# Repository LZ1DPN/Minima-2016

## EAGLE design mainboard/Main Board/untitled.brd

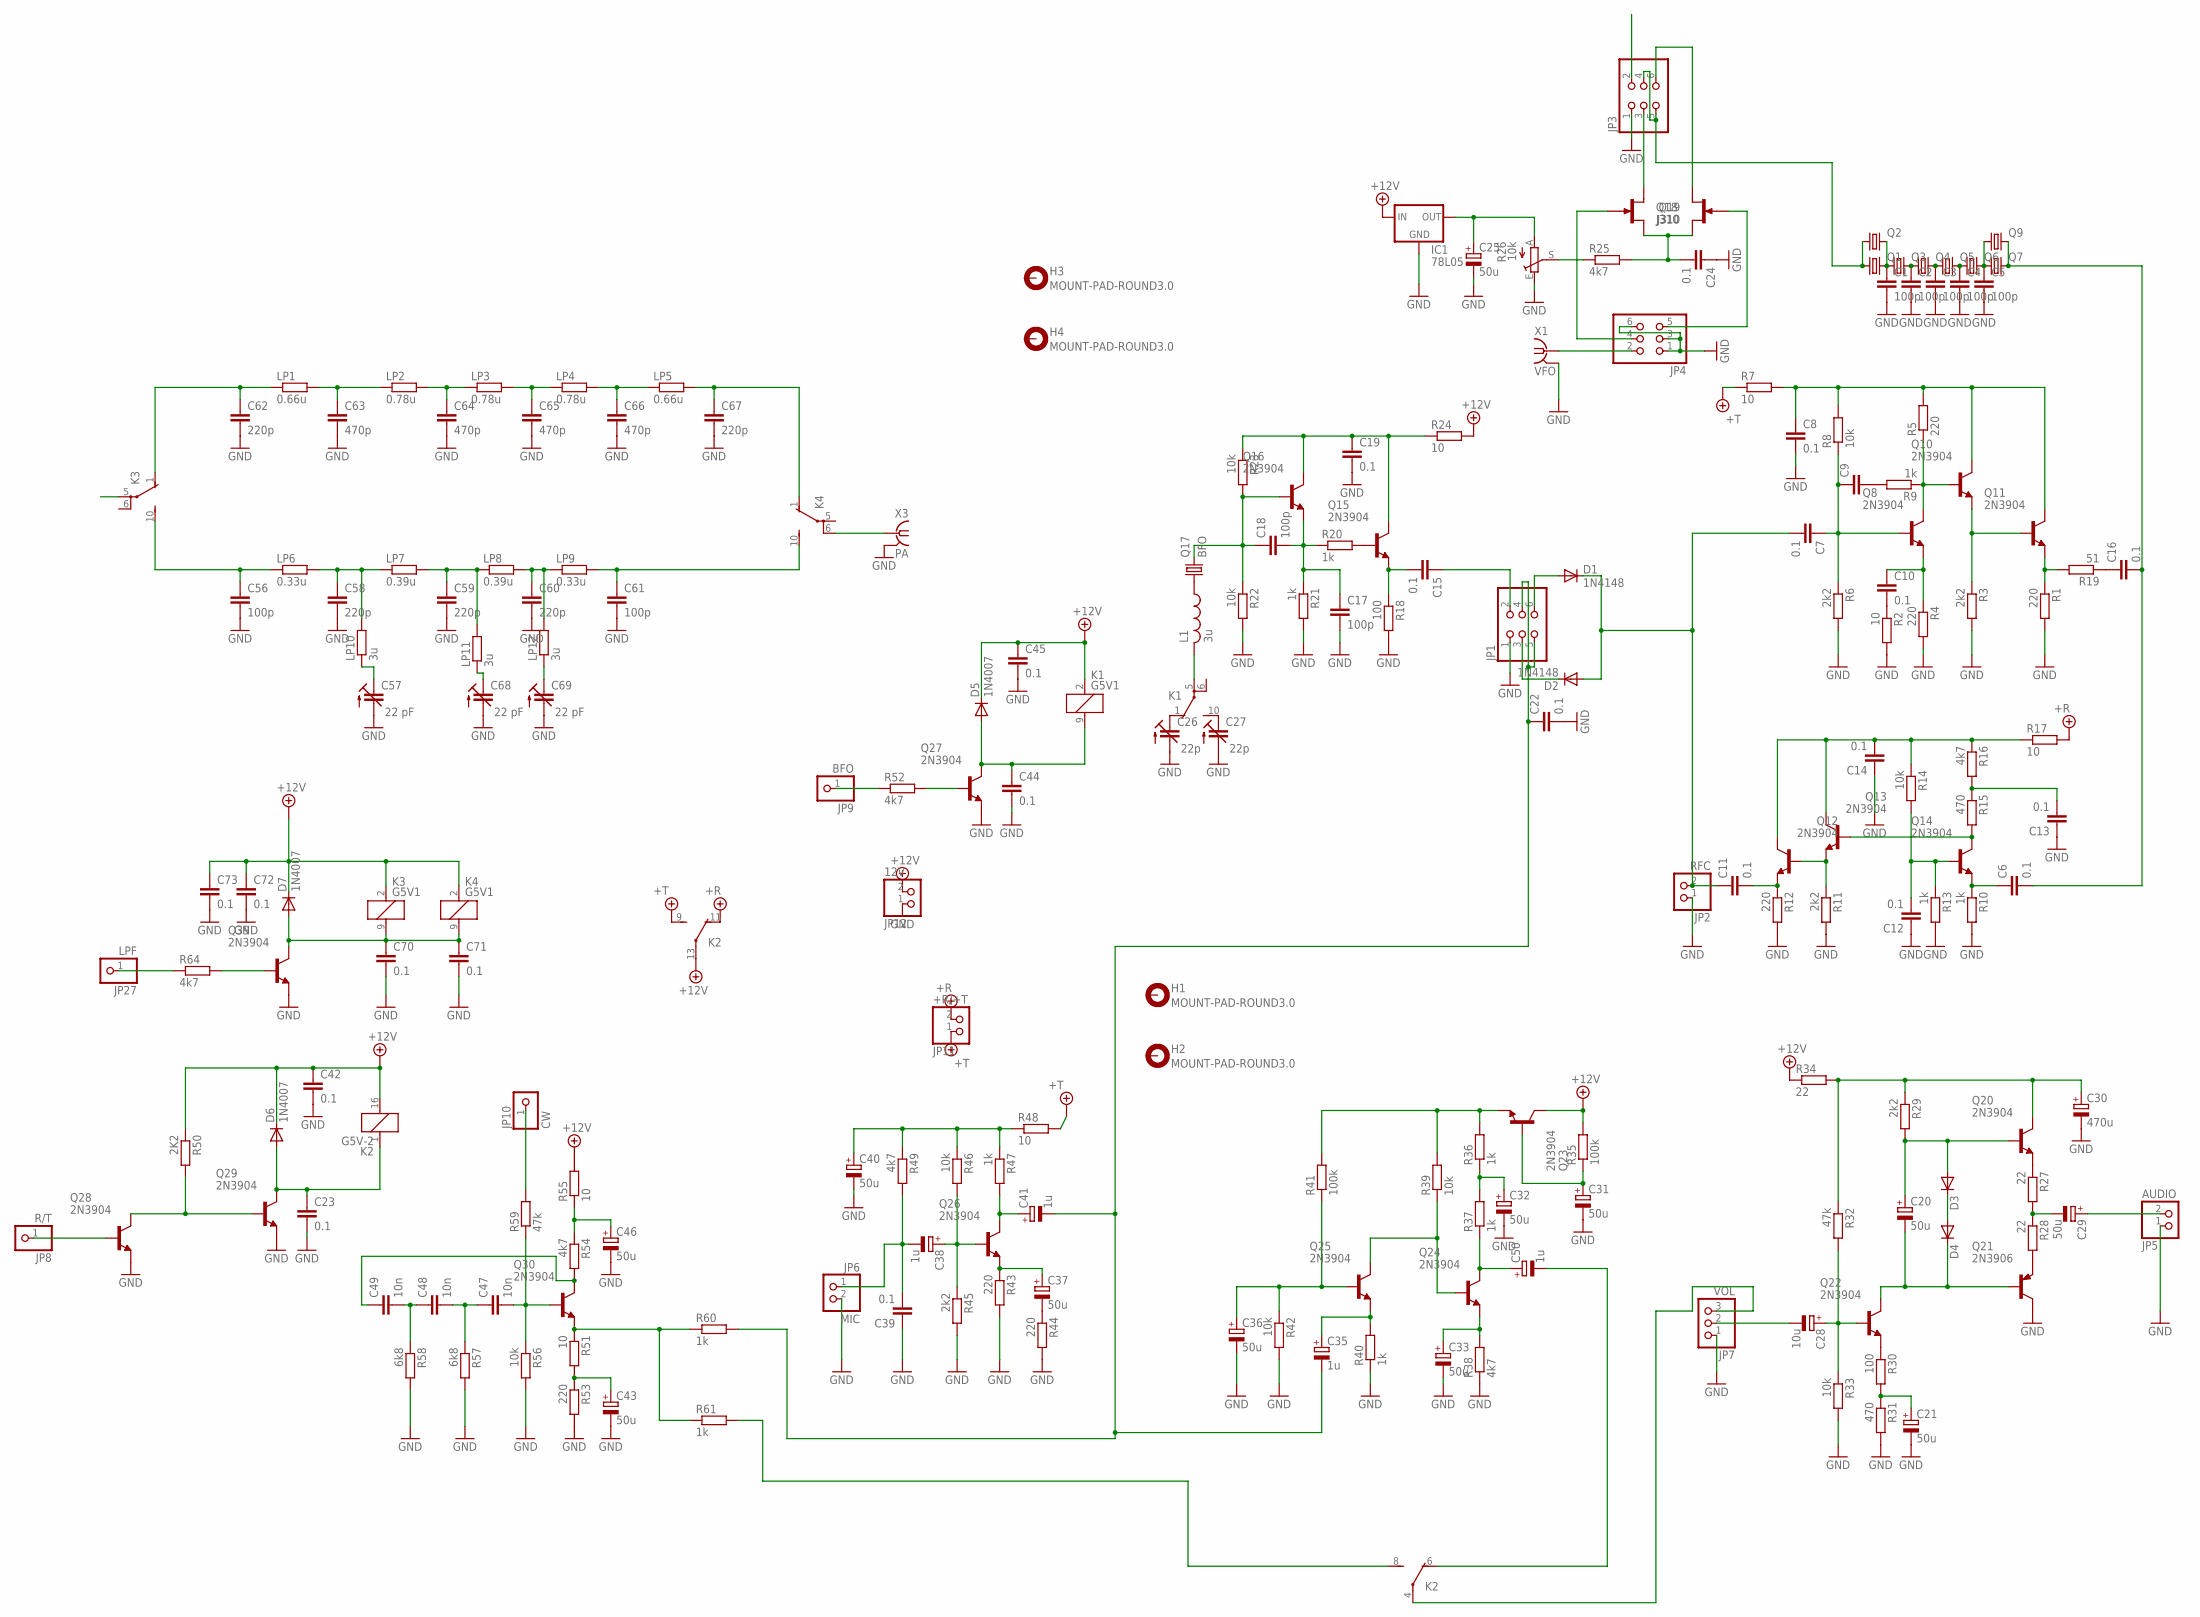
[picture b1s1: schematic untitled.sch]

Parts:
C1, C2, C3, C4, C5: 100p; C1206
C6, C7, C8, C10, C11, C12, C13, C14, C15, C16, C19, C22, C23, C24, C39, C42, C44, C45, C70, C71, C72, C73: 0.1; C050-024X044
C9: C-EU050-024X044; C050-024X044
C17, C18, C56, C61: 100p; C050-024X044
C20, C21, C25, C29, C31, C32, C33, C36, C37, C40, C43, C46: 50u; E2,5-5
C26, C27: 22p; CTRIMTZ03
C28: 10u; E2,5-5
C30: 470u; E2,5-5
C35, C38, C41: 1u; E2,5-5
C47, C48, C49: 10n; C050-024X044
C50: 1u; E5-4
C57, C68, C69: 22 pF; CTRIMTZ03
C58, C59, C60, C62, C67: 220p; C050-024X044
C63, C64, C65, C66: 470p; C050-024X044
D1, D2: 1N4148; D-5
D3, D4: DIODE-D-5; D-5
D5, D6, D7: 1N4007; D-5
H1, H2, H3, H4: MOUNT-PAD-ROUND3.0; 3,0-PAD
IC1: 78L05; 78LXX
JP1, JP3, JP4: PINHD-2X3; 2X03
JP2: RFC; 1X02
JP5: AUDIO; 1X02
JP6: MIC; 1X02
JP7: VOL; 1X03
JP8: R/T; 1X01
JP9: BFO; 1X01
JP10: CW; 1X01
JP11: +R/+T; 1X02
JP12: 12V; 1X02
JP27: LPF; 1X01
K1, K3, K4: G5V1
K2: G5V-2
L1: 3u; 0207/2V
LP1, LP5: 0.66u; 0204/5
LP2, LP3, LP4: 0.78u; 0204/5
LP6, LP9: 0.33u; 0204/5
LP7, LP8: 0.39u; 0204/5
LP10, LP11, LP12: 3u; 0204/5
Q1, Q2, Q3, Q4, Q5, Q6, Q7, Q9: CRYSTALHC49S; HC49/S
Q8, Q10, Q11, Q12, Q13, Q14, Q15, Q16, Q20, Q22, Q23, Q24, Q25, Q26, Q27, Q28, Q29, Q30, Q39: 2N3904; TO92
Q17: BFO; HC49/S
Q18, Q19: J310; TO92R
Q21: 2N3906; TO92
R1, R4, R5, R12, R43, R44, R53: 220; 0204/5
R2, R7, R17, R24, R48, R51, R55: 10; 0204/5
R3, R6, R11, R29, R45: 2k2; 0204/5
R8, R14, R22, R23, R33, R39, R42, R46, R56: 10k; 0204/5
R9, R10, R13, R20, R21, R36, R37, R40, R47, R60, R61: 1k; 0204/5
R15, R31: 470; 0204/5
R16, R25, R38, R49, R52, R54, R64: 4k7; 0204/5
R18, R30: 100; 0204/5
R19: 51; 0204/5
R26: 10k; CA6V
R27, R28, R34: 22; 0204/5
R32, R59: 47k; 0204/5
R35, R41: 100k; 0204/5
R50: 2K2; 0204/5
R57, R58: 6k8; 0204/5
X1: VFO; BU-SMA-V
X3: PA; BU-SMA-V

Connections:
+5V/1: JP11.2, K2.11 (O), R17.2
+5V/2: JP11.1, K2.9 (S), R7.1, R48.2
+12V: C42.1, C45.1, C72.1, C73.1, D5.C, D6.C, D7.C, IC1.IN, JP12.2, K1.2 (1), K2.13, K2.16 (2), K3.2 (1), K4.2 (1), Q23.1 (C), R24.2, R34.1, R35.2, R50.1, R55.2
GND: C1.2, C2.2, C3.2, C4.2, C5.2, C8.2, C12.1, C13.1, C14.1, C17.2, C19.2, C21.-, C22.2, C23.2, C24.1, C25.-, C26.2 (A), C27.2 (A), C30.-, C31.-, C32.-, C33.-, C36.-, C39.1, C40.-, C42.2, C43.-, C44.2, C45.2, C46.-, C56.2, C57.2 (A), C58.2, C59.2, C60.2, C61.2, C62.2, C63.2, C64.2, C65.2, C66.2, C67.2, C68.2 (A), C69.2 (A), C70.2, C71.2, C72.2, C73.2, IC1.GND, JP1.1, JP2.1, JP3.1, JP4.1, JP4.3, JP4.6, JP5.1, JP6.2, JP7.1, JP12.1, Q21.1 (C), Q27.3 (E), Q28.3 (E), Q29.3 (E), Q39.3 (E), R1.2, R2.2, R3.2, R4.2, R6.2, R10.2, R11.2, R12.2, R13.2, R18.2, R21.2, R22.2, R26.E, R31.2, R33.2, R38.1, R40.1, R42.2, R43.2, R44.2, R45.2, R53.2, R56.2, R57.2, R58.2, X1.2 (GND), X1.3 (GND), X1.4 (GND), X1.5 (GND), X3.2 (GND), X3.3 (GND), X3.4 (GND), X3.5 (GND)
unnamed: C1.1, Q1.2, Q2.2, Q3.1
unnamed: C2.1, Q3.2, Q4.1
unnamed: C3.1, Q4.2, Q5.1
unnamed: C4.1, Q5.2, Q6.1
unnamed: C5.1, Q6.2, Q7.1, Q9.1
unnamed: C6.2, C16.2, Q7.2, Q9.2
unnamed: C26.1 (E), K1.1 (O)
unnamed: C10.1, Q8.3 (E), R4.1
unnamed: C10.2, R2.1
unnamed: C7.1, C9.1, Q8.2 (B), R6.1, R8.1
unnamed: Q8.1 (C), Q10.2 (B), R5.1, R9.1
unnamed: Q10.3 (E), Q11.2 (B), R3.1
unnamed: Q11.3 (E), R1.1, R19.2
unnamed: C8.1, Q10.1 (C), Q11.1 (C), R5.2, R7.2, R8.2
unnamed: C16.1, R19.1
unnamed: C9.2, R9.2
unnamed: Q12.2 (B), Q13.3 (E), R11.1
unnamed: C11.2, Q12.3 (E), R12.1
unnamed: C14.2, Q12.1 (C), Q13.1 (C), R14.1, R16.1, R17.1
unnamed: C27.1 (E), K1.10 (S)
unnamed: C12.2, Q14.2 (B), R13.1, R14.2
unnamed: C6.1, Q14.3 (E), R10.1
unnamed: Q13.2 (B), Q14.1 (C), R15.2
unnamed: C13.2, R15.1, R16.2
unnamed: C15.2, Q15.3 (E), R18.1
unnamed: Q15.2 (B), R20.2
unnamed: C17.1, C18.2, Q16.3 (E), R20.1, R21.1
unnamed: C19.1, Q15.1 (C), Q16.1 (C), R23.1, R24.1
unnamed: C15.1, JP1.2
unnamed: C18.1, Q16.2 (B), Q17.2, R22.1, R23.2
unnamed: L1.1, Q17.1
unnamed: K1.5, L1.2
unnamed: R25.1, R26.S
unnamed: Q20.3 (E), R27.1
unnamed: Q27.2 (B), R52.2
unnamed: D1.A, JP1.6
unnamed: D2.C, JP1.3
unnamed: C7.2, C11.1, D1.C, D2.A, JP2.2
unnamed: JP3.4, JP3.5, Q1.1, Q2.1
unnamed: JP3.3, Q18.D
unnamed: JP3.6, Q19.D
unnamed: C24.2, Q18.S, Q19.S, R25.2
unnamed: JP4.5, Q19.G
unnamed: JP4.4, Q18.G
unnamed: C29.-, R27.2, R28.1
unnamed: JP4.2, X1.1
unnamed: Q21.3 (E), R28.2
unnamed: C25.+, IC1.OUT, R26.A
unnamed: D3.C, D4.A
unnamed: C20.-, D4.C, Q21.2 (B), Q22.1 (C)
unnamed: C20.+, D3.A, Q20.2 (B), R29.2
unnamed: C30.+, Q20.1 (C), R29.1, R32.1, R34.2
unnamed: Q22.3 (E), R30.1
unnamed: C21.+, R30.2, R31.1
unnamed: C28.+, Q22.2 (B), R32.2, R33.1
unnamed: C29.+, JP5.2
unnamed: C28.-, JP7.2
unnamed: C31.+, Q23.2 (B), R35.1
unnamed: Q23.3 (E), R36.2, R39.2, R41.2
unnamed: C32.+, R36.1, R37.2
unnamed: C50.+, Q24.1 (C), R37.1
unnamed: C33.+, Q24.3 (E), R38.2
unnamed: Q24.2 (B), Q25.1 (C), R39.1
unnamed: JP9.1, R52.1
unnamed: C35.+, Q25.3 (E), R40.2
unnamed: C36.+, Q25.2 (B), R41.1, R42.1
unnamed: C37.+, Q26.3 (E), R43.1
unnamed: C37.-, R44.1
unnamed: C38.+, Q26.2 (B), R45.1, R46.2
unnamed: C41.+, Q26.1 (C), R47.2
unnamed: C40.+, R46.1, R47.1, R48.1, R49.1
unnamed: C38.-, C39.2, JP6.1, R49.2
unnamed: JP7.3, K2.4
unnamed: C22.1, C35.-, C41.-, JP1.4, JP1.5, R60.2
unnamed: C50.-, K2.6 (O)
unnamed: JP8.1, Q28.2 (B)
unnamed: C23.1, D6.A, K2.1, Q29.1 (C)
unnamed: Q28.1 (C), Q29.2 (B), R50.2
unnamed: C44.1, D5.A, K1.9 (2), Q27.1 (C)
unnamed: C57.1 (E), LP10.1
unnamed: Q30.3 (E), R51.1, R60.1, R61.1
unnamed: C43.+, R51.2, R53.1
unnamed: C49.1, Q30.1 (C), R54.2
unnamed: C46.+, R54.1, R55.1
unnamed: C47.2, Q30.2 (B), R56.1, R59.1
unnamed: C47.1, C48.2, R57.1
unnamed: C48.1, C49.2, R58.1
unnamed: C68.1 (E), LP11.1
unnamed: JP10.1, R59.2
unnamed: K2.8 (S), R61.2
unnamed: C56.1, K3.10 (S), LP6.1
unnamed: C58.1, LP6.2, LP7.1, LP10.2
unnamed: C59.1, LP7.2, LP8.1, LP11.2
unnamed: C60.1, LP8.2, LP9.1, LP12.2
unnamed: C61.1, K4.10 (S), LP9.2
unnamed: C62.1, K3.1 (O), LP1.1
unnamed: C63.1, LP1.2, LP2.1
unnamed: C64.1, LP2.2, LP3.1
unnamed: C65.1, LP3.2, LP4.1
unnamed: C66.1, LP4.2, LP5.1
unnamed: C67.1, K4.1 (O), LP5.2
unnamed: K4.6, X3.1
unnamed: JP3.2, K3.5
unnamed: C69.1 (E), LP12.1
unnamed: Q39.2 (B), R64.2
unnamed: JP27.1, R64.1
unnamed: C70.1, C71.1, D7.A, K3.9 (2), K4.9 (2), Q39.1 (C)

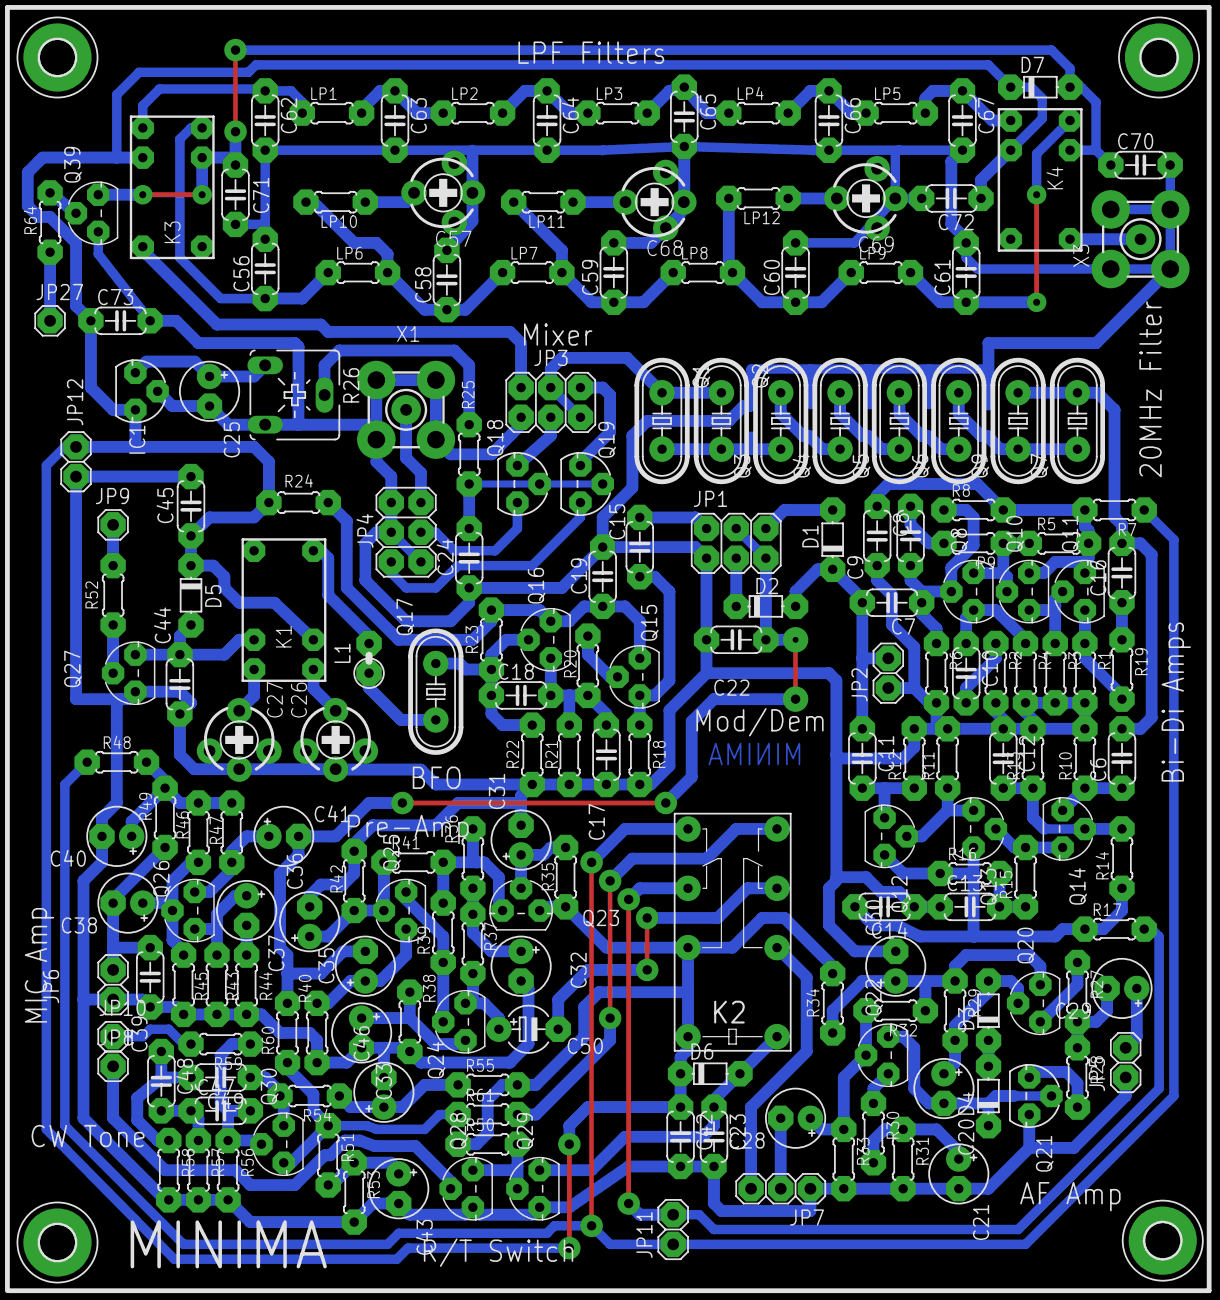
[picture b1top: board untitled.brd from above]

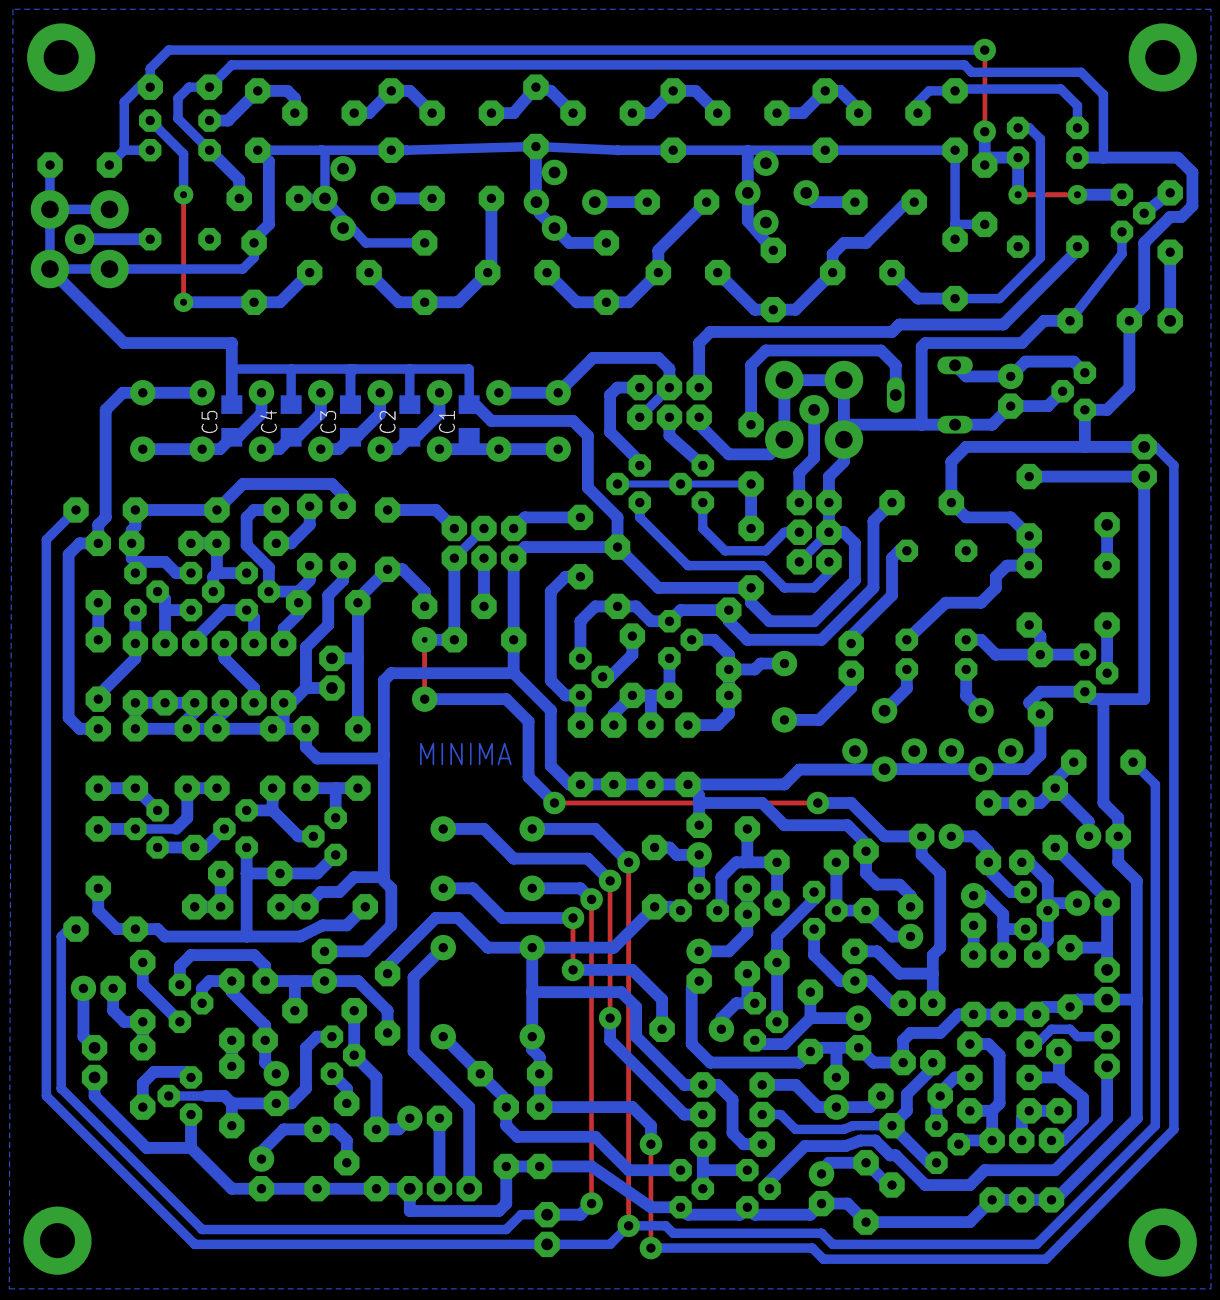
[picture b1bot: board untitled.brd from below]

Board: 2 copper layers, 204 parts (5 on the bottom side), 111 nets.

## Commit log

2016-10-19 :space_invader: Added .gitattributes
2016-10-19 minima
    my minima work docs and arduino sources
2017-03-13 13.03.2017
    13.03.2017
2017-04-20 20.04.2017
    20.04.2017
